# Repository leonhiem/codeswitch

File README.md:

# codeswitch
Codeswitch to open/close a relay

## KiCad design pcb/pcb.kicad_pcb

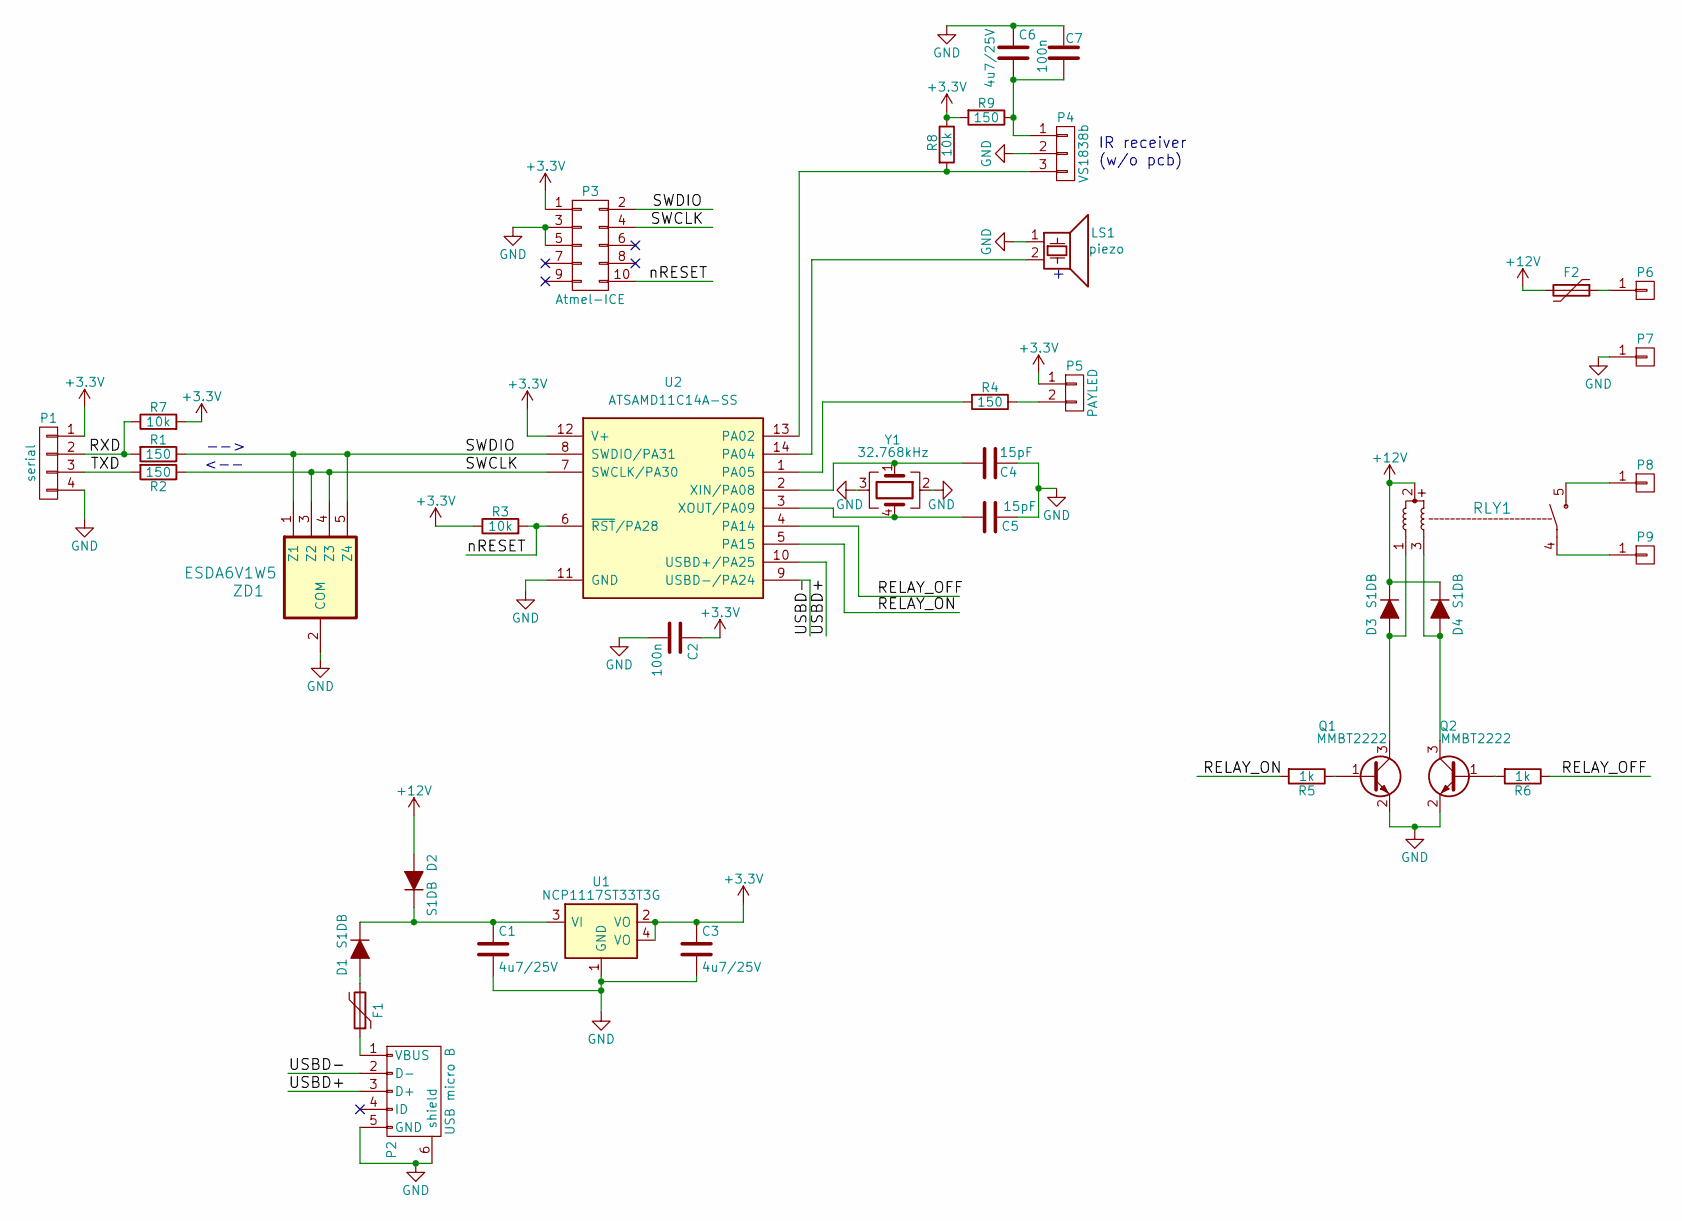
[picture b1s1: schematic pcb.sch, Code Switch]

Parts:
C1, C3, C6: 4u7/25V; C_0805_reflow
C2, C7: 100n; C_0805_reflow
C4, C5: 15pF; C_0805_reflow
D1, D2, D3, D4: S1DB; D_SMB_Handsoldering
F1: Polyfuse 250mA-hold 500mA-trip; Fuse_SMD1206_HandSoldering
F2: Polyfuse 1.1A-hold 2.2A-trip; R_1812
LS1: piezo; MagneticBuzzer_StarMicronics_HMB-06_HMB-12
P1: serial; Pin_Header_Straight_1x04_Pitch2.54mm
P2: USB micro B; USB_Micro-B_10103594-0001LF
P3: Atmel-ICE; Atmel_ICE
P4: VS1838b; Pin_Header_Straight_1x03_Pitch2.54mm
P5: PAYLED; Pin_Header_Straight_1x02_Pitch2.54mm
P6, P7, P8, P9: (faston male 6.35mm); faston_m_63
Q1, Q2: MMBT2222; SOT-23
R1, R2, R4, R9: 150; R_0805_reflow
R3, R7, R8: 10k; R_0805_reflow
R5, R6: 1k; R_0805_reflow
RLY1: RAMWAY_DS903C-90A_12V_D
U1: NCP1117ST33T3G; SOT-223
U2: ATSAMD11C14A-SS; SOIC-14_3.9x8.7mm_Pitch1.27mm
Y1: 32.768kHz; Crystal_SMD_Abracon_4pin_32768khz
ZD1: ESDA6V1W5; SOT-353_SC-70-5_Handsoldering

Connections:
+3V3: C2.1, C3.1, P1.1, P3.1, P5.1, R3.1, R7.2, R8.1, R9.2, U1.2 (VO), U1.4 (VO), U2.12 (V+)
+12V: D2.2 (A), D3.1 (K), D4.1 (K), F2.2, RLY1.2
/RELAY_OFF: R6.1, U2.4 (PA14)
/RELAY_ON: R5.2, U2.5 (PA15)
/RXD: P1.2, R1.2, R7.1
/SWCLK: P3.4, R2.1, U2.7 (SWCLK/PA30), ZD1.3 (Z2), ZD1.4 (Z3)
/SWDIO: P3.2, R1.1, U2.8 (SWDIO/PA31), ZD1.1 (Z1), ZD1.5 (Z4)
/TXD: P1.3, R2.2
/USBD+: P2.3 (D+), U2.10 (USBD+/PA25)
/USBD-: P2.2 (D-), U2.9 (USBD-/PA24)
/nRESET: P3.10, R3.2, U2.6 (~RST~/PA28)
GND: C1.2, C2.2, C3.2, C4.1, C5.1, C6.1, C7.2, LS1.1, P1.4, P2.5 (GND), P2.6 (shield), P3.3, P3.5, P4.2, P7.1, Q1.2 (E), Q2.2 (E), U1.1 (GND), U2.11 (GND), Y1.2, Y1.3, ZD1.2 (COM)
unnamed: C1.1, D1.1 (K), D2.1 (K), U1.3 (VI)
unnamed: C4.2, U2.2 (XIN/PA08), Y1.1
unnamed: C5.2, U2.3 (XOUT/PA09), Y1.4
unnamed: C6.2, C7.1, P4.1, R9.1
unnamed: D1.2 (A), F1.2
unnamed: D3.2 (A), Q1.3 (C), RLY1.1
unnamed: D4.2 (A), Q2.3 (C), RLY1.3
unnamed: F1.1, P2.1 (VBUS)
unnamed: F2.1, P6.1
unnamed: LS1.2, U2.14 (PA04)
unnamed: P4.3, R8.2, U2.13 (PA02)
unnamed: P5.2, R4.1
unnamed: P8.1, RLY1.5
unnamed: P9.1, RLY1.4
unnamed: Q1.1 (B), R5.1
unnamed: Q2.1 (B), R6.2
unnamed: R4.2, U2.1 (PA05)

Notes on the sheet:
IR receiver (w/o pcb)
-->
<--

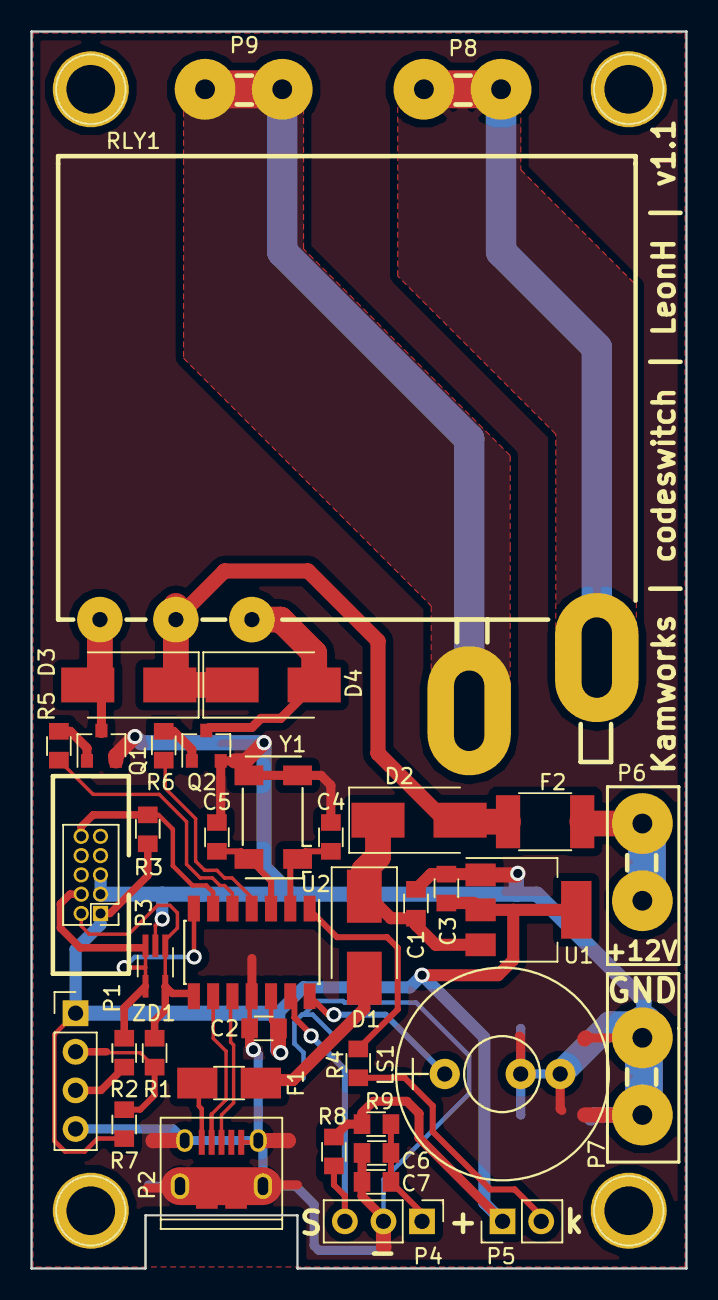
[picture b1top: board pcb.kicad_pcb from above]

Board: 2 copper layers, 43.1 x 81.4 mm, 39 parts (0 on the bottom side), 29 nets.

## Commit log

2021-10-01 commit from working version
